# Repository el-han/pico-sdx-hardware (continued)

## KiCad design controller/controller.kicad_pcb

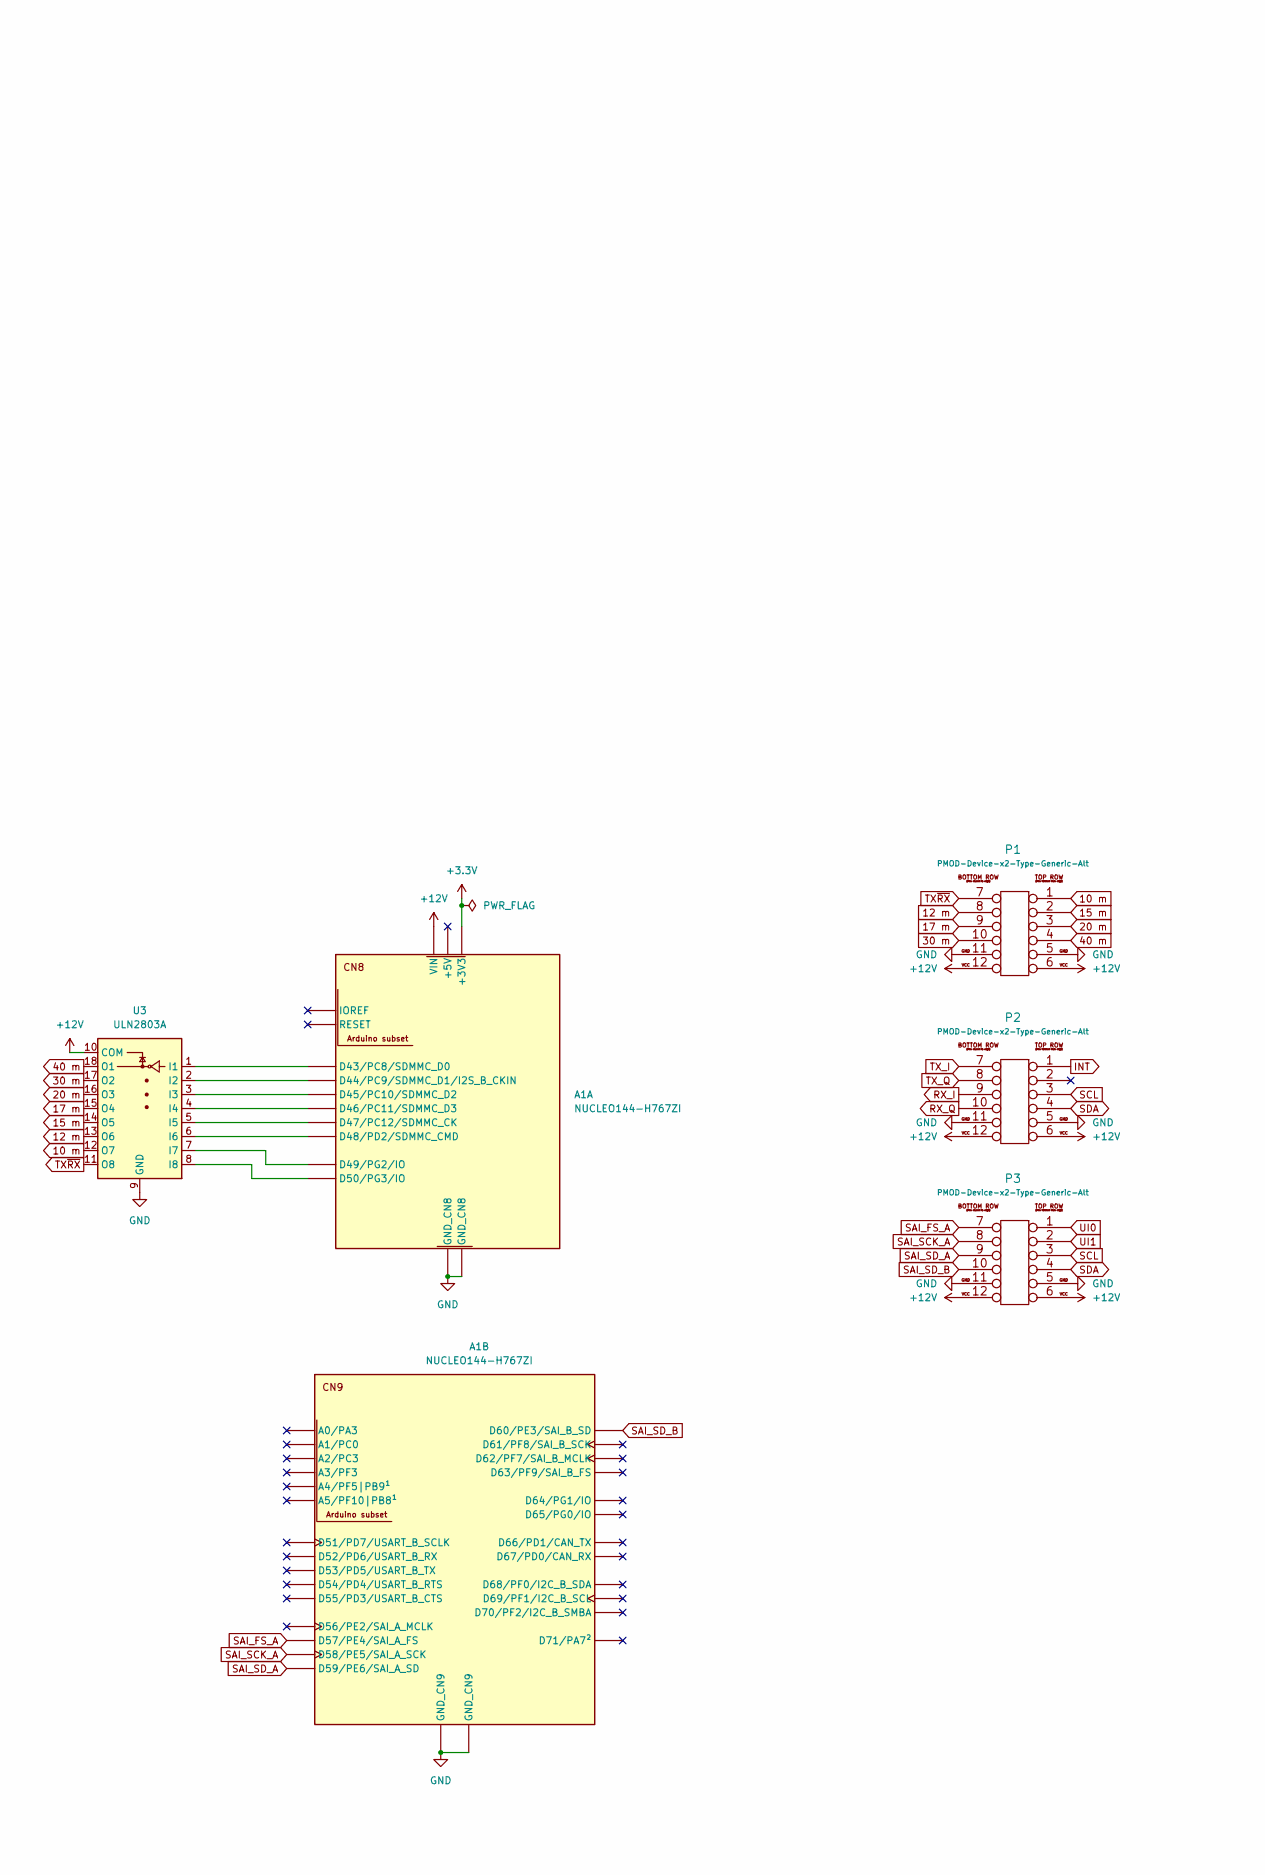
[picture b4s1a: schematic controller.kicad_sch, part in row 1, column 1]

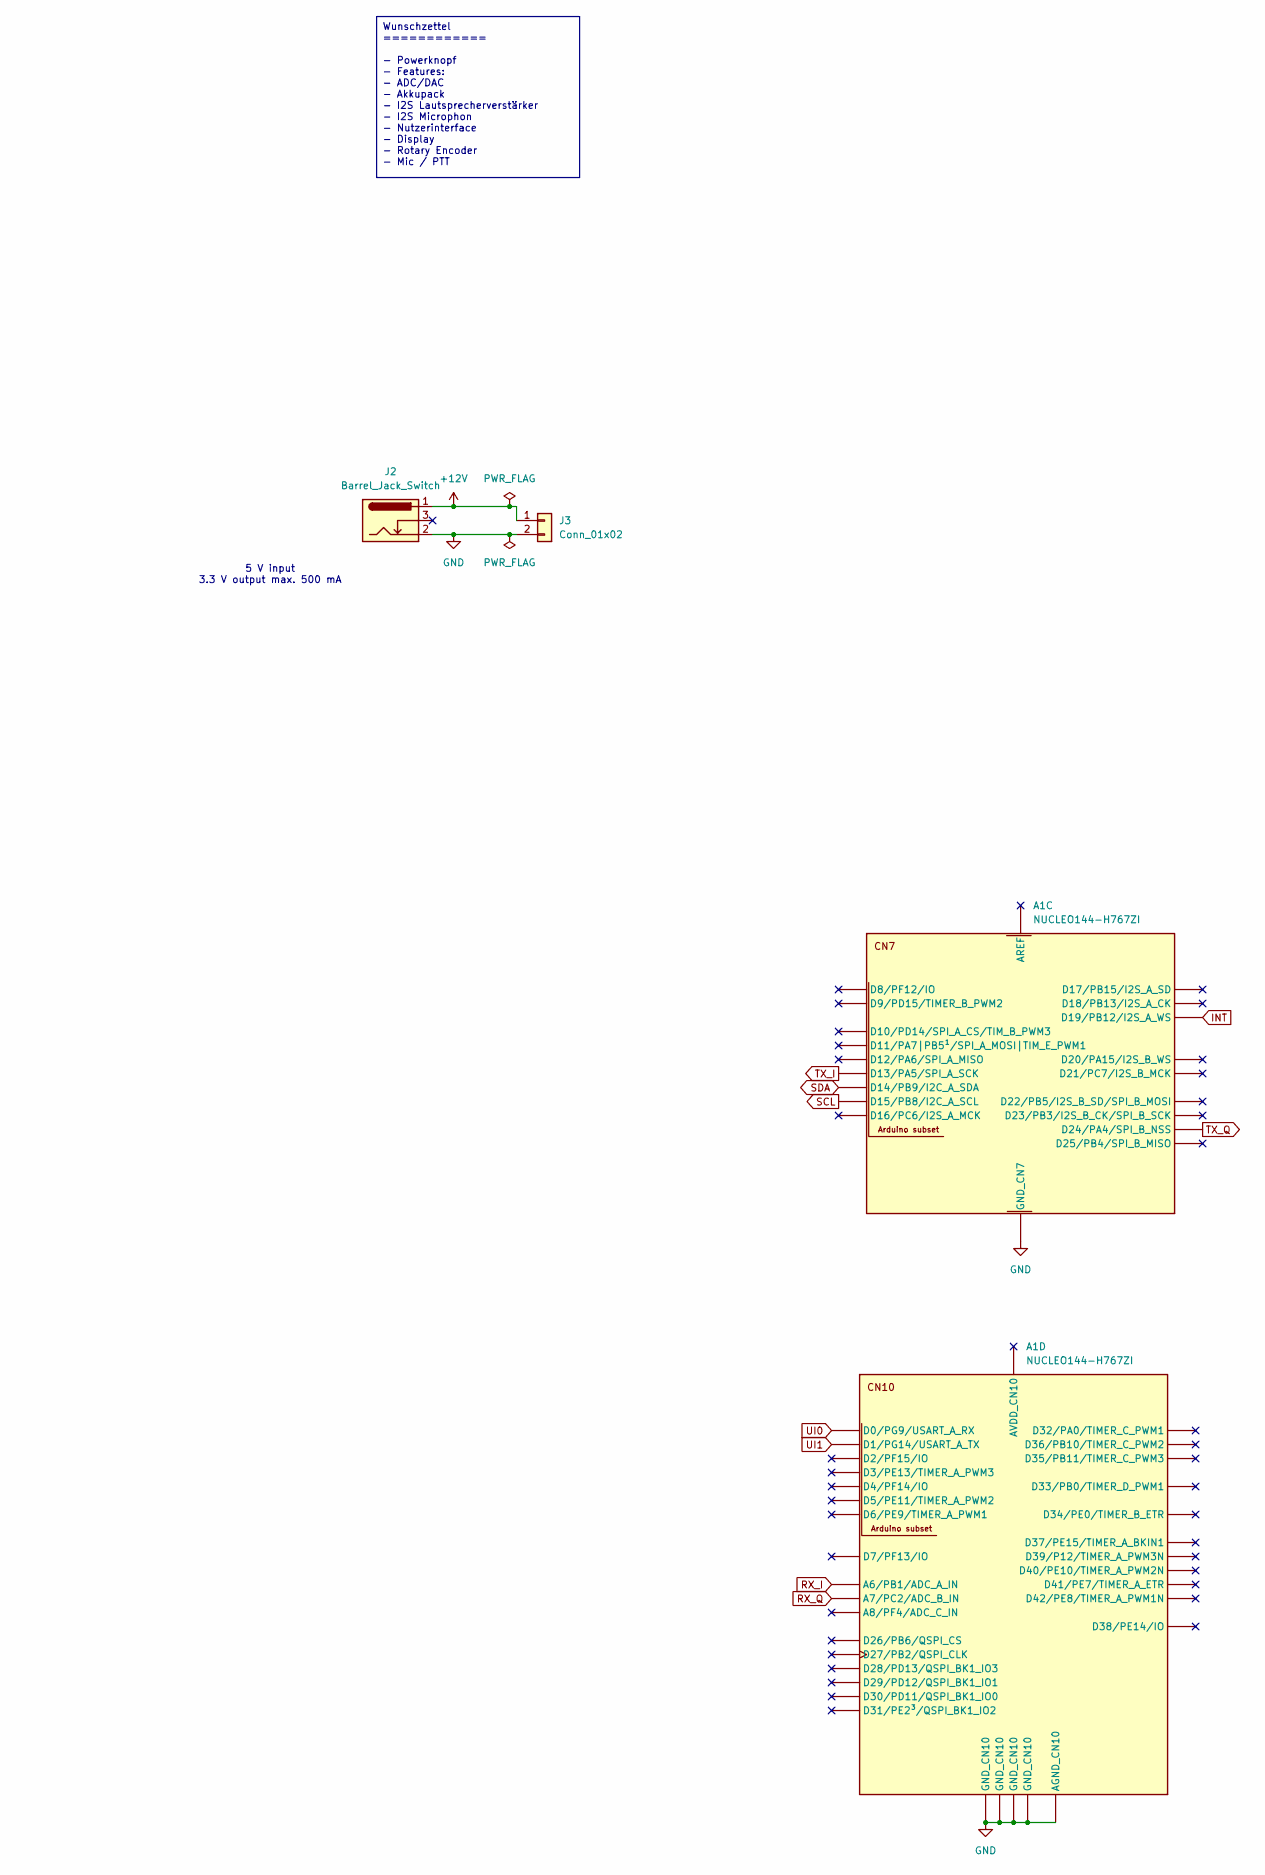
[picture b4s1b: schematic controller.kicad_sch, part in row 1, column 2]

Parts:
A1: NUCLEO144-H767ZI; ST_Zio_Connectors_144_STLink
J2: Barrel_Jack_Switch; BarrelJack_Wuerth_6941xx301002
J3: Conn_01x02; SolderWire-0.75sqmm_1x02_P7mm_D1.25mm_OD3.5mm
P1, P2, P3: PMOD-Device-x2-Type-Generic-Alt; pmod_pin_array_6x2
U3: ULN2803A; SOIC-18W_7.5x11.6mm_P1.27mm

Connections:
10 m: P1.1, U3.12 (O7)
12 m: P1.8, U3.13 (O6)
15 m: P1.2, U3.14 (O5)
17 m: P1.9, U3.15 (O4)
20 m: P1.3, U3.16 (O3)
30 m: P1.10, U3.17 (O2)
40 m: P1.4, U3.18 (O1)
+3.3V: A1.CN8_7 (+3V3)
+12V: A1.CN8_15 (VIN), J2.1, J3.1, P1.6, P1.12, P2.6, P2.12, P3.6, P3.12, U3.10 (COM)
GND: A1.CN7_8 (GND_CN7), A1.CN8_11 (GND_CN8), A1.CN8_13 (GND_CN8), A1.CN9_12 (GND_CN9), A1.CN9_23 (GND_CN9), A1.CN10_3 (AGND_CN10), A1.CN10_5 (GND_CN10), A1.CN10_17 (GND_CN10), A1.CN10_22 (GND_CN10), A1.CN10_27 (GND_CN10), J2.2, J3.2, P1.5, P1.11, P2.5, P2.11, P3.5, P3.11, U3.9 (GND)
INT: A1.CN7_7 (D19/PB12/I2S_A_WS), P2.1
unnamed: A1.CN8_2 (D43/PC8/SDMMC_D0), U3.1 (I1)
unnamed: A1.CN8_4 (D44/PC9/SDMMC_D1/I2S_B_CKIN), U3.2 (I2)
unnamed: A1.CN8_6 (D45/PC10/SDMMC_D2), U3.3 (I3)
unnamed: A1.CN8_8 (D46/PC11/SDMMC_D3), U3.4 (I4)
unnamed: A1.CN8_10 (D47/PC12/SDMMC_CK), U3.5 (I5)
unnamed: A1.CN8_12 (D48/PD2/SDMMC_CMD), U3.6 (I6)
unnamed: A1.CN8_14 (D49/PG2/IO), U3.7 (I7)
unnamed: A1.CN8_16 (D50/PG3/IO), U3.8 (I8)
RX_I: A1.CN10_7 (A6/PB1/ADC_A_IN), P2.9
RX_Q: A1.CN10_9 (A7/PC2/ADC_B_IN), P2.10
SAI_FS_A: A1.CN9_16 (D57/PE4/SAI_A_FS), P3.7
SAI_FS_B: A1.CN9_28 (D63/PF9/SAI_B_FS)
SAI_MCLK_A: A1.CN9_14 (D56/PE2/SAI_A_MCLK)
SAI_MCLK_B: A1.CN9_26 (D62/PF7/SAI_B_MCLK)
SAI_SCK_A: A1.CN9_18 (D58/PE5/SAI_A_SCK), P3.8
SAI_SCK_B: A1.CN9_24 (D61/PF8/SAI_B_SCK)
SAI_SD_A: A1.CN9_20 (D59/PE6/SAI_A_SD), P3.9
SAI_SD_B: A1.CN9_22 (D60/PE3/SAI_B_SD), P3.10
SCL: A1.CN7_2 (D15/PB8/I2C_A_SCL), P2.3, P3.3
SDA: A1.CN7_4 (D14/PB9/I2C_A_SDA), P2.4, P3.4
TX_I: A1.CN7_10 (D13/PA5/SPI_A_SCK), P2.7
TX_Q: A1.CN7_17 (D24/PA4/SPI_B_NSS), P2.8
TX~RX: P1.7, U3.11 (O8)
UI0: A1.CN10_16 (D0/PG9/USART_A_RX), P3.1
UI1: A1.CN10_14 (D1/PG14/USART_A_TX), P3.2

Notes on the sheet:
Wunschzettel ============ - Powerknopf - Features: - ADC/DAC - Akkupack - I2S Lautsprecherverstärker - I2S Microphon - Nutzerinterface - Display - Rotary Encoder - Mic / PTT
5 V input 3.3 V output max. 500 mA

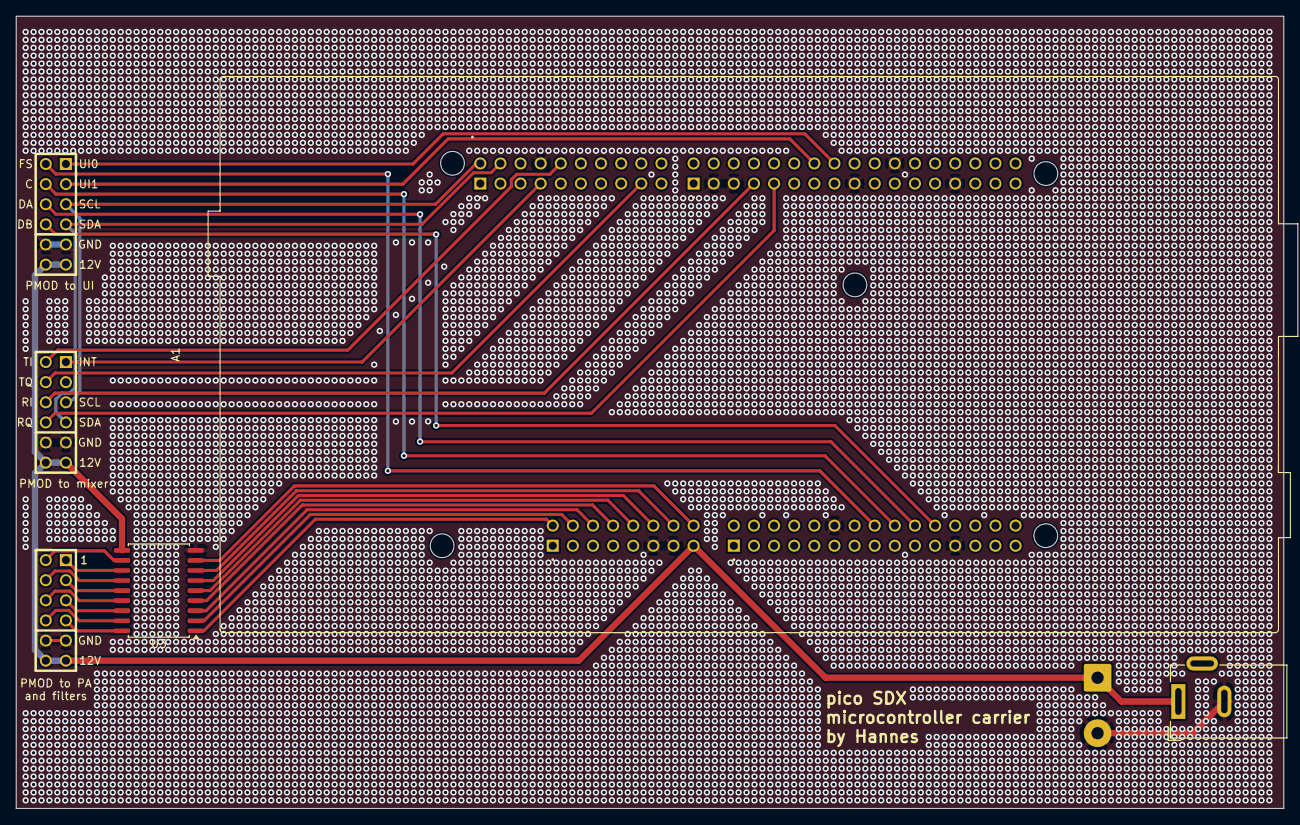
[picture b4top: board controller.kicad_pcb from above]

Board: 2 copper layers, 160.0 x 100.0 mm, 7 parts (0 on the bottom side), 31 nets.

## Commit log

2024-02-10 add oscillator, upmixer and downmixer. power WIP
2024-02-11 update clock module footprint
2024-02-11 add documentation and RaspberryPi Pico
2024-03-05 routed with filter relays without PA
2024-03-22 add active lowpass filter in upconverter branch
2024-03-22 add presentation slides on which this transceiver is based
2024-04-21 modular design
2024-06-18 mixer routed
2024-06-21 clean up
2024-06-21 add bandpass filter board
2024-06-21 add mixer board
2024-08-27 use lt1117 as linear voltage regulator
2024-08-27 add microcontroller board
2024-08-27 remove USB HS PHY
2024-08-27 add PA
2024-08-27 replace 7806 by 1117
2024-08-27 replace RF connectors, add missing silkscreen text
2024-10-14 use ZIO footprint for Nucleo
2024-10-14 add Makefile
2024-10-14 add gerber parameters for jlcpcb
2024-10-14 add .gitignore
2024-10-14 remove external symbol and footprint libraries
2024-10-14 fix deletion
2024-10-14 add .gitignore and Makefile
2024-10-14 add gerber export settings and get drc-clean
2024-10-14 drc clean
2024-10-14 clean up libraries
2024-10-29 add README.md from external repository
2026-05-19 Add license file
